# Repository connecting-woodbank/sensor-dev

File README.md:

README
======
The Connecting Woodbank project aims to create a wireless sensor network for monitoring growing conditions to reduce inefficiencies within small-scale agriculture.  It is comprised of a network of sensor nodes based around an Arduino board conected to a series of sensors and a short range radio.

Sensors
=======
The sensor nodes each contain sensors for measuring:
- soil temperature
- soil relative moisture
- air temperatue
- air relative humidity
- light level (Red, Green and Blue wavelengths)
- infra-red radiation

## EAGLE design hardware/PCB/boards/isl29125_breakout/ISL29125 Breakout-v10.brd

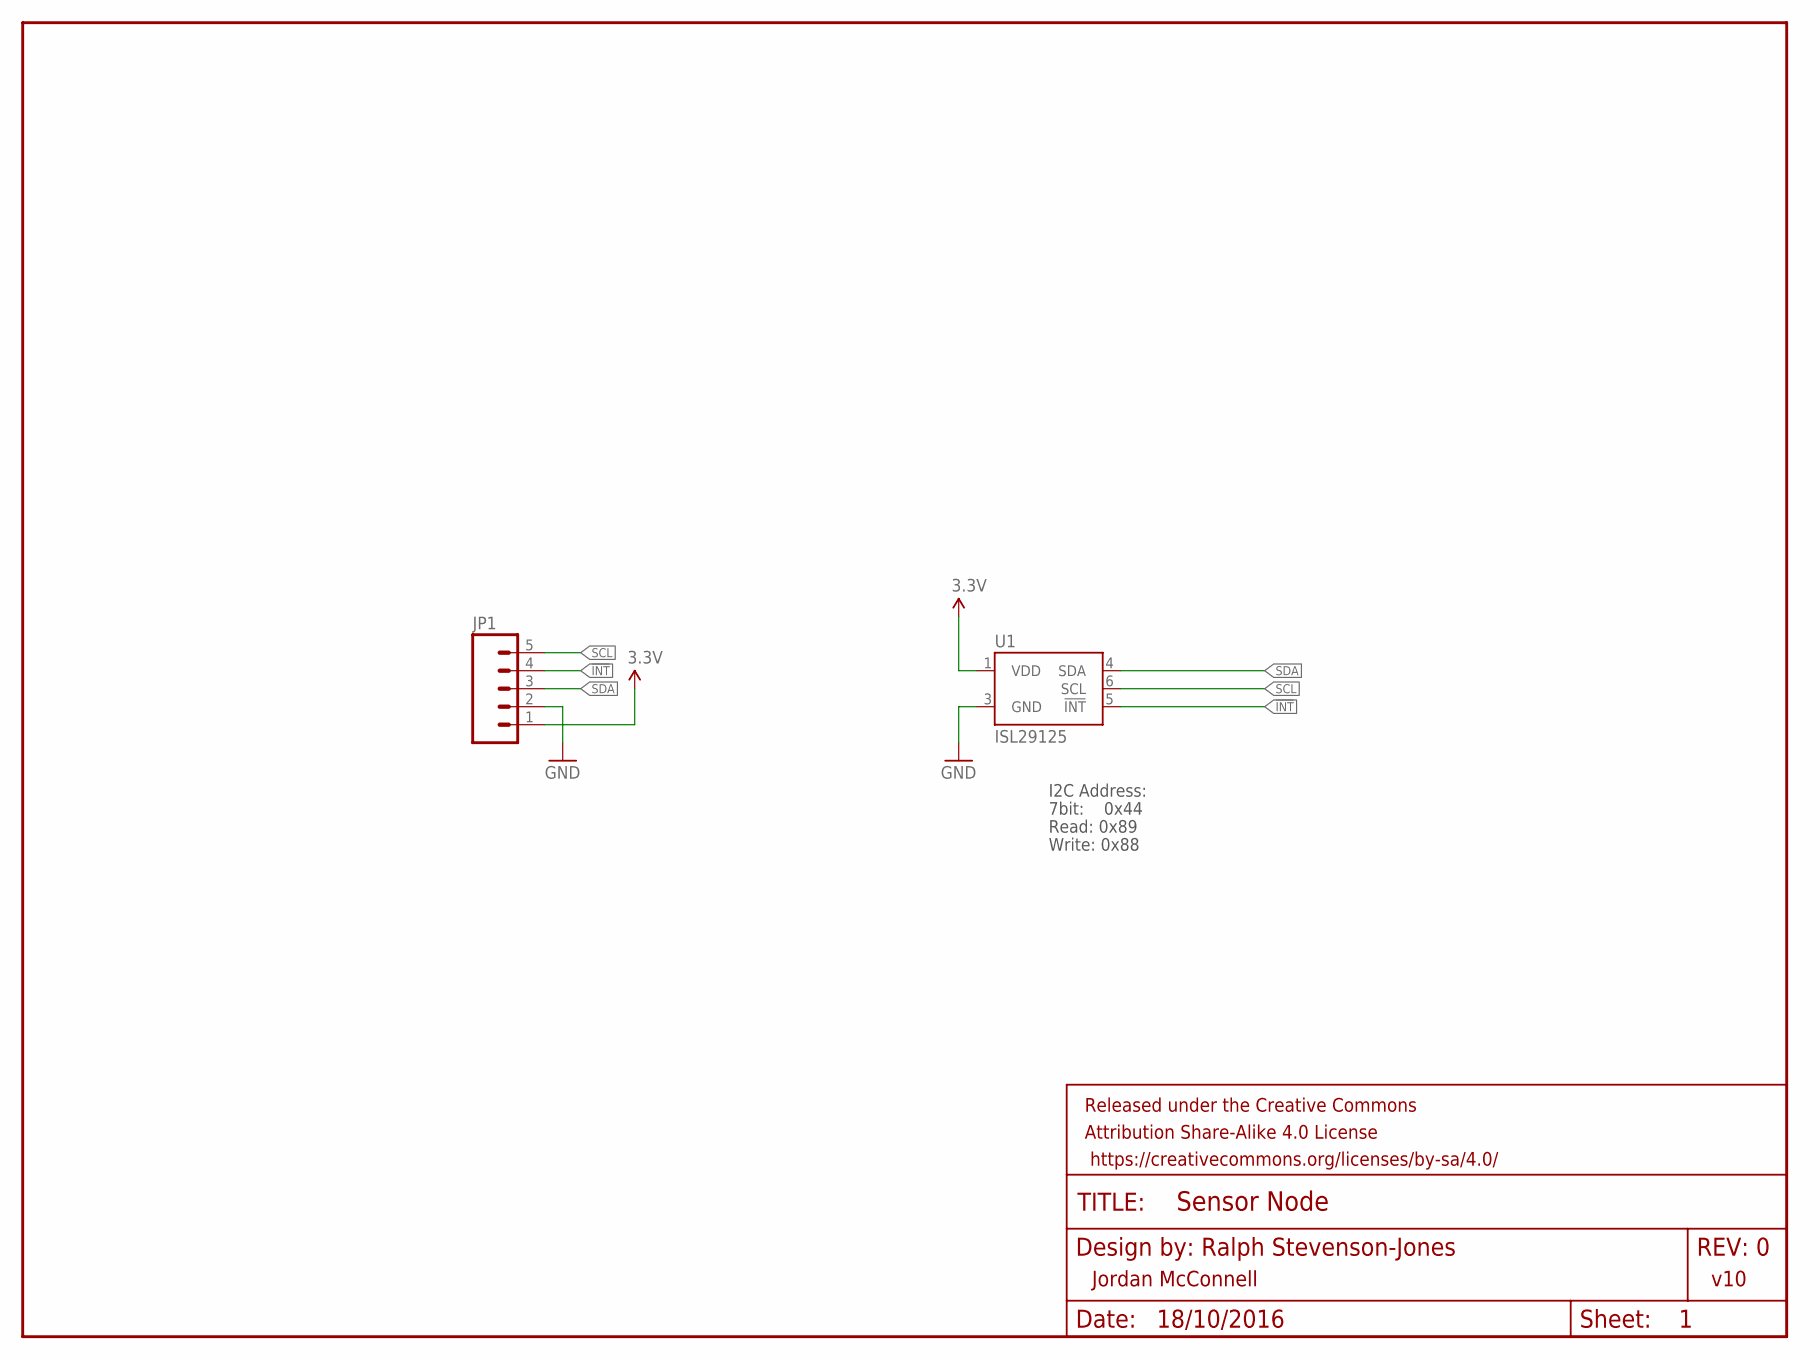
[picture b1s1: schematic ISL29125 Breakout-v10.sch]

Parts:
FRAME1: FRAME-LETTER; CREATIVE_COMMONS
JP1: M05PTH; 1X05
U1: ISL29125; ODFN-LD-6

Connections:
3.3V: JP1.1, U1.1 (VDD)
!INT: JP1.4, U1.5 (!INT)
GND: JP1.2, U1.3 (GND)
SCL: JP1.5, U1.6 (SCL)
SDA: JP1.3, U1.4 (SDA)

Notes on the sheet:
Jordan McConnell
v10
7bit: 0x44
I2C Address:
Read: 0x89
Write: 0x88

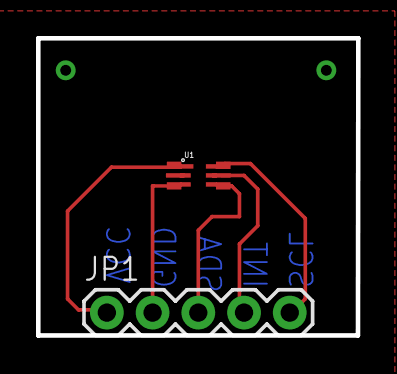
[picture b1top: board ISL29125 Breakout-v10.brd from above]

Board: 2 copper layers, 17.8 x 16.5 mm, 3 parts (0 on the bottom side), 5 nets.

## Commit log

2016-07-28 Update README file
2016-08-17 Added sensor code
2016-08-17 Format code
    sensors.ino updated and formatted of clarity
2016-08-17 Create gh-pages branch via GitHub
2016-08-17 LICENCE added
2016-08-17 README updated
    Added basic project information to README file
2016-08-17 REAMDE moved
2016-08-17 separated serial print
    separated serial print functions from the sensor read functions. This
    is to allow values to be sent through the radio as (multiple) 8-bit
    values.
2016-08-19 Reformatted output
    - created msg[] character array to hold data for data transmission
    - formatted and populated msg[] array with upper and lower bytes of
    message variables
2016-08-19 Updated for compatibility with Mini
    - defined baud rate using macro
    - included #ifdef condition to set clock rate for mini to support 8MHz
    cock rate on 3.3V mini
2016-10-24 Added ISL29125 shield
    - restructured file layout (added hardware/software folders)
    - added ISL29125 board
    - amended pads for ease of soldering
2016-10-26 Updated GEM file
2016-10-26 Test mode
    test function of sensors within node without reading values
    (initilisation only)
2016-10-28 Test I2 C line
    The I2C line was tested with the new PCB and it was found that the I2C
    bus would not return data. Test data is added and analysed.
    TO DO
    - amend clock rate of the I2C bus. There appears to be extra
    capacitance in the line. Attempt to amend this by reducing clock rate
    of the I2C bus. At present the arduino is using the default rate of
2016-10-28 Bitscope guide
    - added guide to bitscope data analysis
2016-10-28 Updated sensors.ino
    - deleted test function print
2016-11-01 added sensor test figure
    - tesing I2C bus illustration of error source
2017-01-11 added ISL29125 library files
2017-01-11 removed library files
2017-01-11 added library files
2017-01-12 added library files to libraries folder and to project folder
2017-01-12 removed local library files - instead use machine library. additiona libraries can be installed from the /libraries folder
2017-01-12 updated serial baud rate and library links
2017-01-12 added notes on using arduino on linux
2017-01-12 updated DHT checksum code and formatted data readout
2017-01-12 added mac notes for arudion re. drivers, serial read
2017-01-12 moved mac notes
2017-01-17 added Nrf2401 example code
2017-01-17 added RF code
2017-01-17 moced examle RF code
2017-01-18 updated mac arduino guide
2017-01-18 added additinal arduino libraries
2017-01-18 updated sensors standalone firmware
2017-01-18 updated readout on server side

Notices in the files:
parts and their libraries:
SparkFun-Aesthetics: Licensing: Creative Commons ShareAlike 4.0 International - https://creativecommons.org/licenses/by-sa/4.0
SparkFun-Aesthetics: Released under the Creative Commons Attribution Share-Alike 4.0 License
SparkFun-Aesthetics: https://creativecommons.org/licenses/by-sa/4.0
